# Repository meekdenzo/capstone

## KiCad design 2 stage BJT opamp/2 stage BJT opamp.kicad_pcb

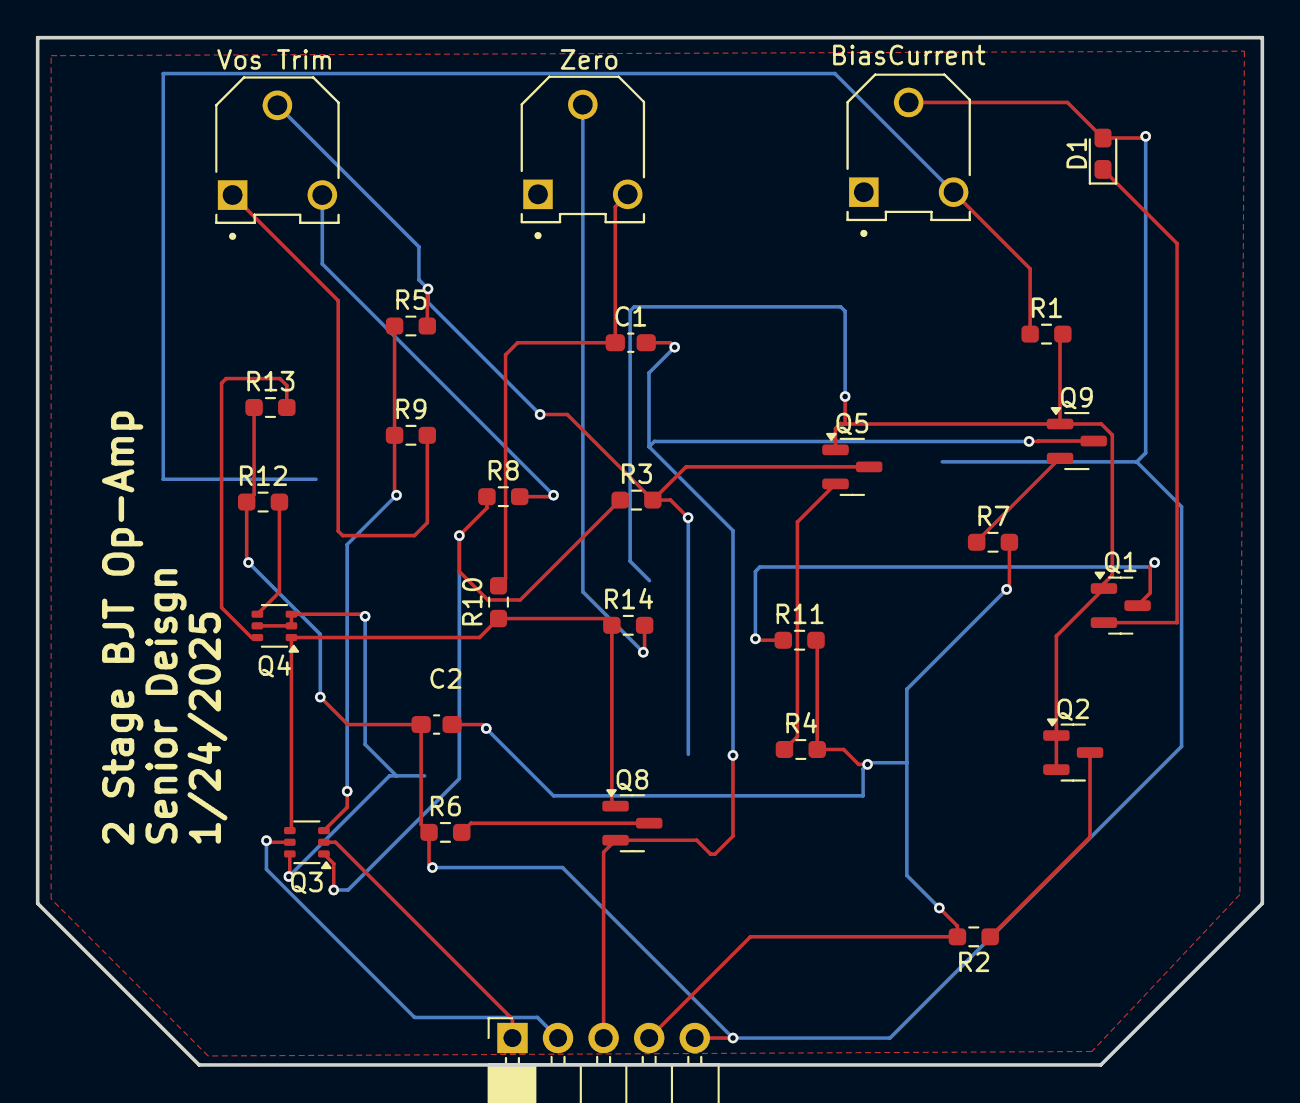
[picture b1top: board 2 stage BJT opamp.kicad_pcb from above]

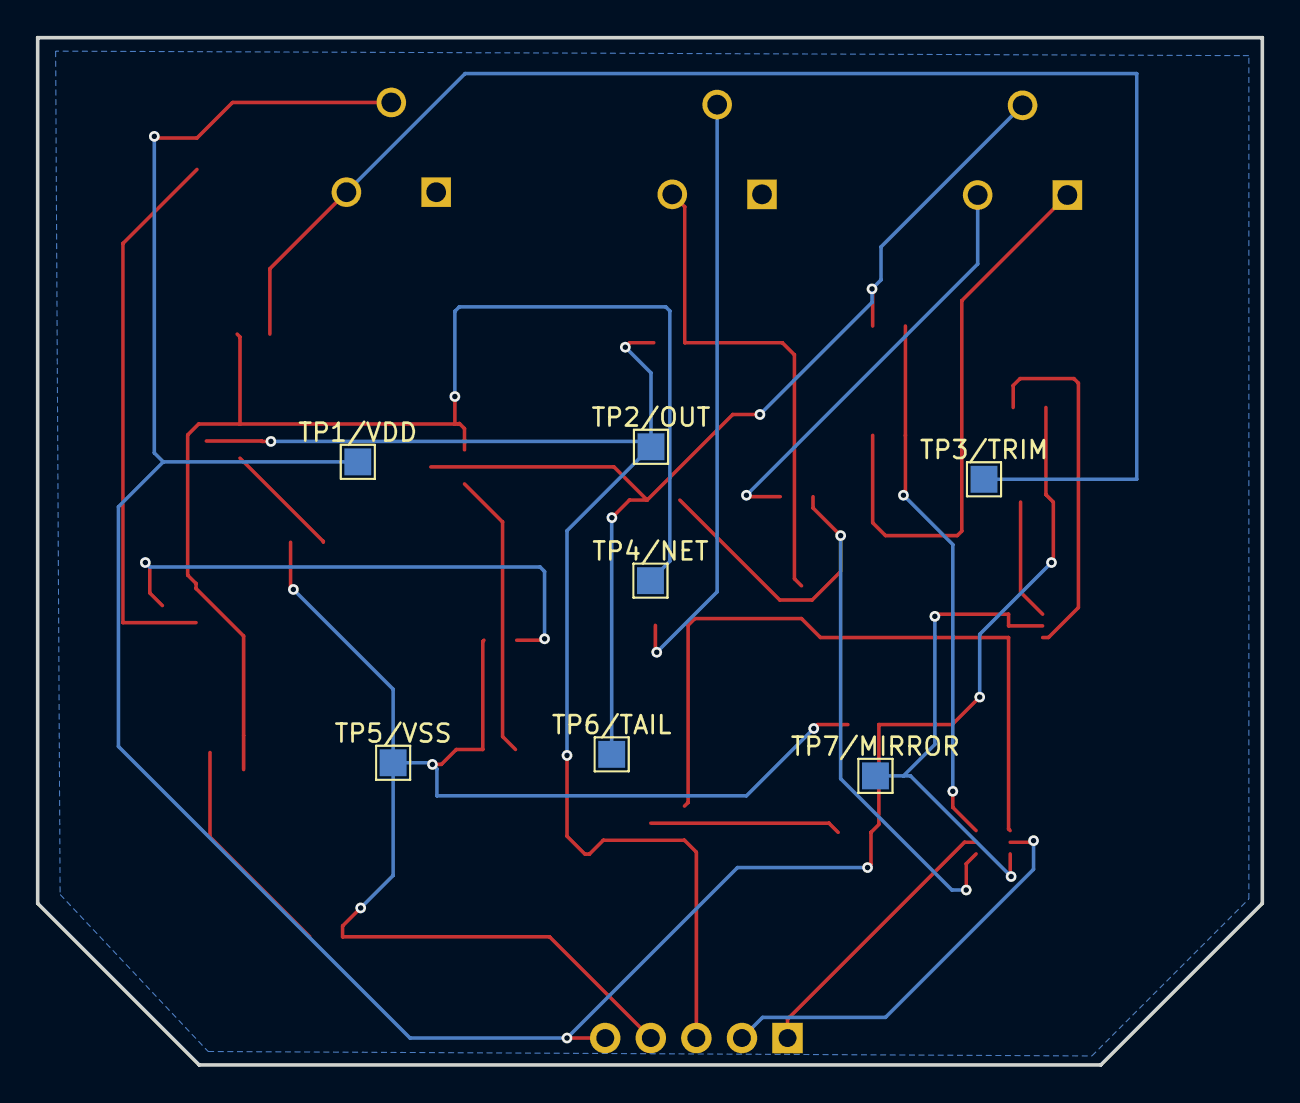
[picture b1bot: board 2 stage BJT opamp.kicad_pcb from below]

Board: 2 copper layers, 68.2 x 57.2 mm, 35 parts (7 on the bottom side), 24 nets.

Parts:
BiasCurrent: 500 Ω; TRIM_3306F-1-501
C1: 0.001 uF; C_0603_1608Metric_Pad1.08x0.95mm_HandSolder
C2: 10 uF; C_0603_1608Metric_Pad1.08x0.95mm_HandSolder
D1: LED; LED_0603_1608Metric_Pad1.05x0.95mm_HandSolder
J1: Conn_01x05; PinSocket_1x05_P2.54mm_Horizontal
Q1, Q2, Q5, Q9: MMBT3904; SOT-23
Q3: MMDT3904; SOT-363_SC-70-6
Q4: MMDT3906; SOT-363_SC-70-6
Q8: MMBT3906; SOT-23
R1: 680 Ω; R_0603_1608Metric_Pad0.98x0.95mm_HandSolder
R2, R4, R6, R7, R11, R12, R13, R14: 10; R_0603_1608Metric_Pad0.98x0.95mm_HandSolder
R3, R5: 220; R_0603_1608Metric_Pad0.98x0.95mm_HandSolder
R8, R9: 100; R_0603_1608Metric_Pad0.98x0.95mm_HandSolder
R10: DNP; R_0603_1608Metric_Pad0.98x0.95mm_HandSolder
TP1/VDD, TP2/OUT, TP3/TRIM, TP4/NET, TP5/VSS, TP6/TAIL, TP7/MIRROR: TestPoint; TestPoint_Pad_1.5x1.5mm
Vos Trim: -500 Ω; TRIM_3306F-1-501
Zero : -500 Ω; TRIM_3306F-1-501

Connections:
/DIFFERENCE: Q3.4 (E2), Q4.1 (E1), Q8.1 (B), R10.1, R14.1
/MIRROR: Q3.6 (C1), Q4.2 (B1), Q4.3 (C2), Q4.5 (B2), TP7/MIRROR.1
/TAIL: Q5.3 (C), R3.2, R5.2, TP6/TAIL.1, Vos Trim.2
/TRIM: BiasCurrent.3, R1.1, TP3/TRIM.1
unnamed: C1.1, R10.2, Zero.3
unnamed: D1.1 (K), Q1.2 (E)
unnamed: Q1.1 (B), Q2.1 (B), Q2.2 (E), Q5.1 (B), Q9.1 (B), R1.2, TP4/NET.1
unnamed: Q1.3 (C), R11.1
unnamed: Q2.3 (C), R2.1
unnamed: Q3.1 (E1), R3.1, R8.1
unnamed: Q3.3 (C2), R5.1, R9.1
unnamed: Q4.6 (C1), R13.2
unnamed: Q4.4 (E2), R12.2
unnamed: Q5.2 (E), R4.1
unnamed: Q8.3 (C), R6.2
unnamed: Q9.2 (E), R7.1
unnamed: R8.2, Vos Trim.3
unnamed: R9.2, Vos Trim.1
unnamed: R14.2, Zero.2
OUT: C1.2, J1.3, Q8.2 (E), Q9.3 (C), TP2/OUT.1
V+: J1.2, Q3.5 (B2)
V-: J1.1, Q3.2 (B1)
VDD: BiasCurrent.2, C2.1, D1.2 (A), J1.5, R6.1, R12.1, R13.1, TP1/VDD.1
VSS: C2.2, J1.4, R2.2, R4.2, R7.2, R11.2, TP5/VSS.1

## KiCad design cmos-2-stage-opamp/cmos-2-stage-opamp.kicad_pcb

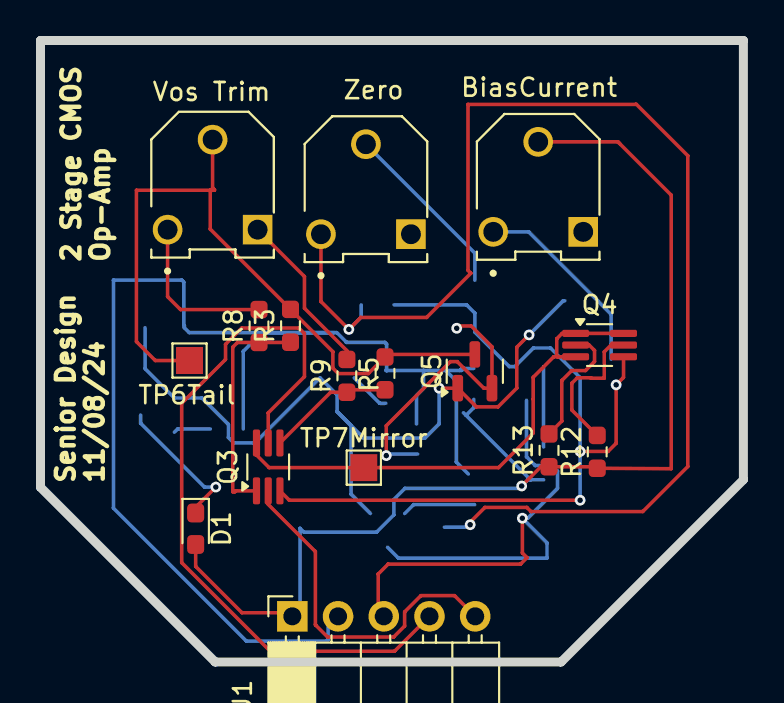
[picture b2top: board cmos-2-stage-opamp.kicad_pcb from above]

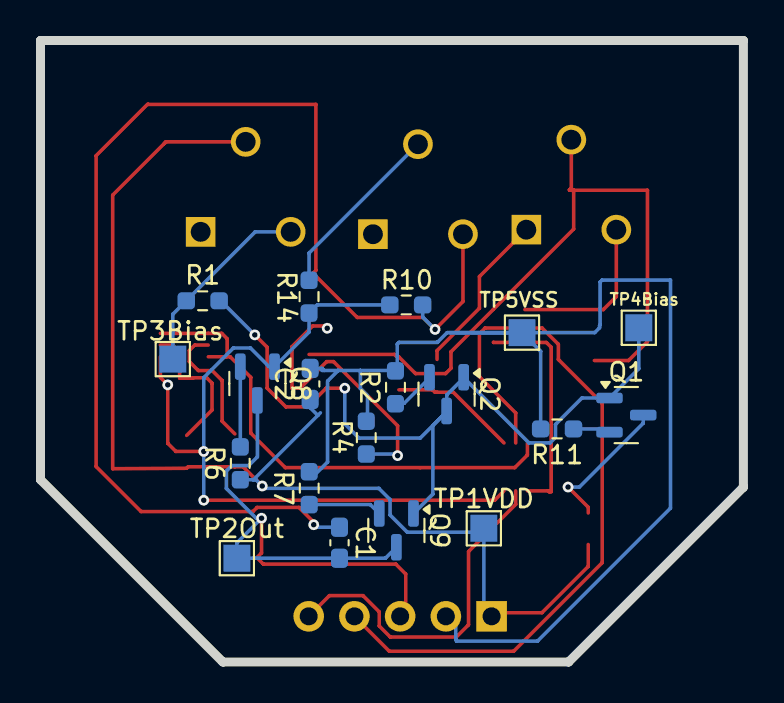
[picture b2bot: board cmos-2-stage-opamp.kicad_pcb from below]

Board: 2 copper layers, 39.0 x 34.5 mm, 35 parts (19 on the bottom side), 24 nets.

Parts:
BiasCurrent: 500Ω; TRIM_3306F-1-501
C1: 0.001µF; C_0603_1608Metric_Pad1.08x0.95mm_HandSolder
C2: 10µF; C_0603_1608Metric_Pad1.08x0.95mm_HandSolder
D1: LED; D_0603_1608Metric_Pad1.05x0.95mm_HandSolder
J1: Conn_01x05; PinSocket_1x05_P2.54mm_Horizontal
Q1, Q2, Q5, Q9: DMN62DOU; SOT-23
Q3: DMN2004DMK-7; SOT-363_SC-70-6_Handsoldering
Q4: DMP2240UDM-7; SOT-363_SC-70-6_Handsoldering
Q8: DMP510DL; SOT-23
R1: 680Ω; R_0603_1608Metric_Pad0.98x0.95mm_HandSolder
R2, R4, R6, R7, R11, R12, R13, R14: 10; R_0603_1608Metric_Pad0.98x0.95mm_HandSolder
R3, R5: 220; R_0603_1608Metric_Pad0.98x0.95mm_HandSolder
R8, R9: 100; R_0603_1608Metric_Pad0.98x0.95mm_HandSolder
R10: DNP; R_0603_1608Metric_Pad0.98x0.95mm_HandSolder
TP1VDD, TP2Out, TP3Bias, TP4Bias, TP5VSS, TP6Tail, TP7Mirror: TestPoint; TestPoint_Pad_1.5x1.5mm
Vos Trim: -500Ω; TRIM_3306F-1-501
Zero : -500Ω; TRIM_3306F-1-501

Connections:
/difference: Q3.3 (DP), Q4.4 (DP), Q8.1 (G), R10.1, R14.1
/mirror: Q3.6 (DN), Q4.1 (GN), Q4.3 (GP), Q4.6 (SN), TP7Mirror.1
/tail: Q5.3 (D), R3.2, R5.2, TP6Tail.1, Vos Trim.2
/trim: BiasCurrent.3, R1.1, TP3Bias.1
unnamed: C1.1, R10.2, Zero.3
unnamed: D1.1 (K), Q1.3 (D)
unnamed: Q1.1 (G), Q2.1 (G), Q2.3 (D), Q5.1 (G), Q9.1 (G), R1.2, TP4Bias.1
unnamed: Q1.2 (S), R11.1
unnamed: Q2.2 (S), R2.1
unnamed: Q3.1 (SN), R3.1, R8.1
unnamed: Q3.4 (SP), R5.1, R9.1
unnamed: Q4.5 (DN), R12.2
unnamed: Q4.2 (SP), R13.2
unnamed: Q5.2 (S), R4.1
unnamed: Q8.2 (D), R6.2
unnamed: Q9.2 (S), R7.1
unnamed: R8.2, Vos Trim.3
unnamed: R9.2, Vos Trim.1
unnamed: R14.2, Zero.2
OUT: C1.2, J1.3, Q8.3 (S), Q9.3 (D), TP2Out.1
V+: J1.4, Q3.5 (GP)
V-: J1.5, Q3.2 (GN)
VDD: BiasCurrent.2, C2.1, D1.2 (A), J1.1, R6.1, R12.1, R13.1, TP1VDD.1
VSS: C2.2, J1.2, R2.2, R4.2, R7.2, R11.2, TP5VSS.1

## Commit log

2024-11-07 nehemiah testing
    this is our first github test
2024-11-07 testing new kicad project
2024-11-08 Parts
2024-11-08 cleanup: added annotations for tp + board images
    DRC passed
    Ready to submit to OSHPark
2024-11-10 final update on board
    added senior design and date approved to chip using silkscreen.
    added name of chip 2 stage cmos op-amp.
    updated footprint of chip from 2.00 1*05 pin conn to 2.54 1*05 pin conn.
    ran DRC and everything checks out perfectly.
2024-11-18 update to names of rv1, rv2, rv3 of board
2024-11-22 add `.gitignore` file
2025-08-04 2 Stage BJT Op-Amp
    These are files for the 2 Stage BJT Op-Amp with BOM and board files.
